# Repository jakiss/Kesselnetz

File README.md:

# Kesselbox
For the enlish version see below.

Das Projekt befasst sich mit der Entwicklung eines Radmessers nach der Idee des Tagesspiegel Berlin (Vgl. https://interaktiv.tagesspiegel.de/radmesser/ und https://github.com/tagesspiegel/radmesser). 

Die genaue des Beschreibung des Projekts mit Grundidee und Annahmen findet sich unter Projektbeschreibung.pdf, um eine kurze Zusammenfassung zu erhalten empfiehlt sich die Datei Zusammenfassung_Projektbeschreibung.pdf.

Das Projekt darf unter der GNU General Public License (GPL) verwendet werden.

------------------------------------------------------------
English version:

The project deals with the development of a measurement system for the overtaking distance between cars and bicycles after the idea of the Tagesspeigel Berlin (see https://interaktiv.tagesspiegel.de/radmesser/ and https://github.com/tagesspiegel/radmesser).

The detailed description of the project including the main idea and assumptions  can be found in Projektbeschreibung.pdf. For a short summary of the topic the file Zusammenfassung_Projektbeschreibung.pdf is recommended.

The project can be reused under the GNU General Public License (GPL).

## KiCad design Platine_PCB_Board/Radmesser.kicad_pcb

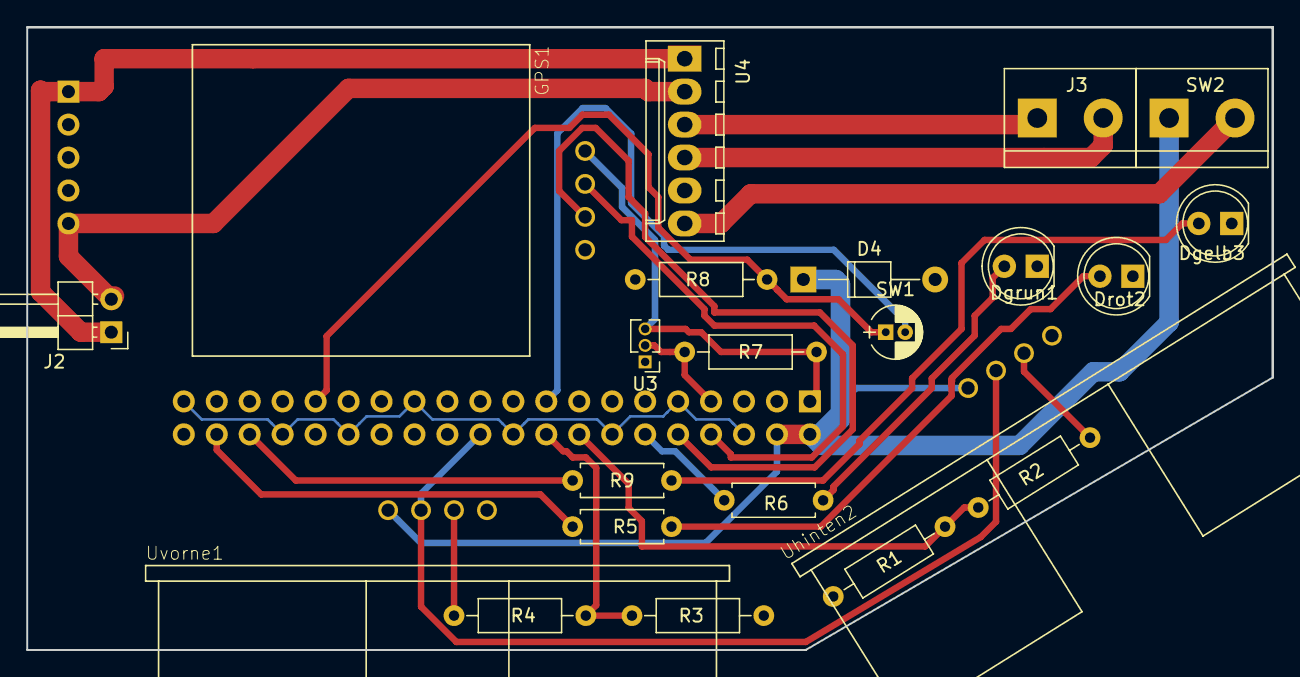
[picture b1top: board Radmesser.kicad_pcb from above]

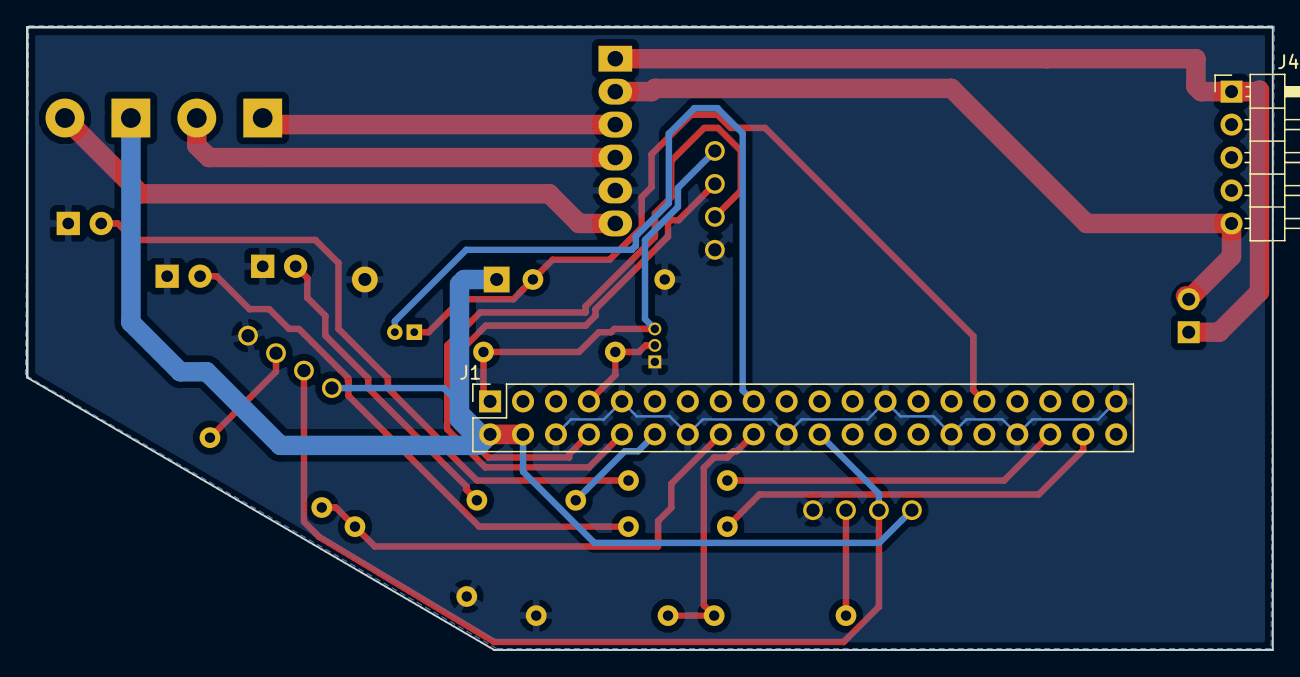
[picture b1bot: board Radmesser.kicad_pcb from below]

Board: 2 copper layers, 96.0 x 48.0 mm, 24 parts (2 on the bottom side), 24 nets.

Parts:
D4: Z5,1V; D_T-1_P10.16mm_Horizontal
Dgelb3: LED; LED_D5.0mm
Dgrun1: LED; LED_D5.0mm
Drot2: LED; LED_D5.0mm
GPS1: GY-GPS6MV2; GY-GPS6MV
J1: Raspberry_Pi_2_3; Raspi_Zero
J2: Conn_01x02_Female; Pin_Header_Angled_1x02_Pitch2.54mm
J3: Conn_01x02_Female; TerminalBlock_bornier-2_P5.08mm
J4: USB_B_Micro; Pin_Header_Angled_1x05_Pitch2.54mm
R1, R3: 1k; R_Axial_DIN0207_L6.3mm_D2.5mm_P10.16mm_Horizontal
R2, R4: 510; R_Axial_DIN0207_L6.3mm_D2.5mm_P10.16mm_Horizontal
R5, R6, R9: 100; R_Axial_DIN0207_L6.3mm_D2.5mm_P7.62mm_Horizontal
R7: 4,7k; R_Axial_DIN0207_L6.3mm_D2.5mm_P10.16mm_Horizontal
R8: 10k; R_Axial_DIN0207_L6.3mm_D2.5mm_P10.16mm_Horizontal
SW1: SW_DIP_x01; CP_Radial_D4.0mm_P1.50mm
SW2: SW_on_off; TerminalBlock_bornier-2_P5.08mm
U3: DS18B20; Pin_Header_Straight_1x03_Pitch1.27mm
U4: Battery_Charging; BatCharging
Uhinten2: HC-SR04; XCVR_HC-SR04
Uvorne1: HC-SR04; XCVR_HC-SR04

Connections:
GND: D4.2, Dgelb3.1, Dgrun1.1, Drot2.1, GPS1.4, J1.6, J1.9, J1.14, J1.20, J1.25, J1.30, J1.34, J1.39, R1.2, R3.2, R8.2, U3.1, U4.5, Uhinten2.4, Uvorne1.4
unnamed: D4.1, J1.2, J1.4, SW2.1, Uhinten2.1, Uvorne1.1
unnamed: Dgelb3.2, R9.2
unnamed: Dgrun1.2, R6.2
unnamed: Drot2.2, R5.2
unnamed: GPS1.1, J1.1, R7.1, U3.3
unnamed: GPS1.2, J1.8
unnamed: GPS1.3, J1.10
unnamed: J1.7, R7.2, U3.2
unnamed: J1.12, R6.1
unnamed: J1.16, R1.1, R2.2
unnamed: J1.17, SW1.2
unnamed: J1.18, R3.1, R4.2
unnamed: J1.22, Uhinten2.2, Uvorne1.2
unnamed: J1.31, R8.1, SW1.1
unnamed: J1.36, R9.1
unnamed: J1.38, R5.1
unnamed: J2.1, J4.1, U4.1
unnamed: J2.2, J4.5, U4.2
unnamed: J3.1, U4.3
unnamed: J3.2, U4.4
unnamed: R2.1, Uhinten2.3
unnamed: R4.1, Uvorne1.3
unnamed: SW2.2, U4.6

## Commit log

2021-03-03 Changes to upset part one
2021-03-07 Added information on Data-definition
2021-03-10 readme created, added sample data
2021-03-10 edited Adressresolve readme
2021-03-10 Erkennungssoftware readme
2021-05-02 KiCad files added
2021-05-04 PCB-Files moved to Hardware folder
2021-05-05 added PCB-Files
2021-05-10 3d-print-data added
